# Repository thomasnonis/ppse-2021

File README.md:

# Abstract
This is the repository for SALMO, the Solar Azimuth and eLevation Motorized lOcator. It is a PCB used for driving a tracking solar panel system, using GPS location and a MPPT algorithm to maximise the incident power.  
The official name of the project is `PPS2021_SUN_TRK`

# About the project
During the second semester of the 2021/2022 A.Y. of their bachelor degree in Electronics Engineering, a group of students known as _SALMO SOCIETY_, developed a custom board to solve real world problems. 
<br>Nowadays, we are all aware about climate change and it's impact, so the _SALMO SOCIETY_ decided in partecipate to the renewable energy run, in particular exploiting the energy obtained by a solar panel to drive a load.
<br>The aim of the board it's to move the solar panel using two step motors (along z-y axis) facilitating the MPP (Maximum Power Point) reaching and, as consequence, delivering the maximum power to the load.<br> Using a GPS module, the board knows exactly where it is located around the globe; afterwards the position of the sun is computed with a specific algorithm based on astronomical calculations. Then, the spatial position of the panel is derived by the accelerometer and compass modules; lastly, the motor is moved in order to follow the exact position of the sun (given its azimuth and elevation).

# Repo structure

    📂 SALMO_pico_fw    -> Firmware 
    📂 datasheets       -> Datasheet of every component mounted on board
    📂 kicad-project    -> KiCad and gerber files 
    
# :rainbow: Building process

Debian:

    sudo apt install cmake gcc-arm-none-eabi libnewlib-arm-none-eabi build-essential

Fedora:

    sudo dnf install cmake
    sudo dnf group install "C Development Tools and Libraries" "Development Tools"
    sudo dnf install gcc-arm-linux-gnu \
    arm-none-eabi-gcc-cs-c++ \
    arm-none-eabi-gcc-cs \
    arm-none-eabi-binutils \
    arm-none-eabi-newlib

then:

    git pull
    git submodule update --init --recursive

now add to your shell profile (`~/.bashrc` or `~/.zshrc`) the current directory (pico-sdk folder) as env variable:
 
`export PICO_SDK_PATH=<path_to>/pico-sdk`

Windows:

Follow this [guide](https://shawnhymel.com/2096/how-to-set-up-raspberry-pi-pico-c-c-toolchain-on-windows-with-vs-code/#Install_MinGW-w64_GCC_Tools) and you're good to go.

Finally, in order to compile:

    cd SALMO_pico_fw
    mkdir build
    cd build 
    cmake ..
    cd src
    make -j4

After this process some binaries files will be created. <br>The suitable one is the `.uf2` file, which is located into `SALMO_pico_fw/build/src`.<br>
Now you can start the board in bootloader mode:
1. Disconnect the board
1. Hold the `BOOTSEL` button
1. Connect the device to your computer

Then drag and drop the `.uf2` file to `RPI-RP2` mass storage device.

## Picotool
If you want to install picotool and easily flash when RP2040 is not in BOOTSEL mode, you need to follow these steps:

### Debian:

    sudo apt install build-essential pkg-config libusb-1.0-0-dev

### Fedora:

    sudo dnf install libusb-devel libusb libusb1-devel systemd-devel
    sudo reboot

### Mac:

    xcode-select --install
    brew install libusb
    brew link --overwrite libusb
    
### Windows:    
For now Picotool doesn't seem to work on Windows, skip these steps and flash "manually" moving the `.uf2` file.

### Compiling Picotool
After you have downloaded picotool you have to compile it:

    cd picotool
    mkdir build
    cd build
    cmake ..
    make

Afterwards, you must give execution permissions to the scripts:

    cd ../../SALMO_pico_fw/src
    sudo chmod +x build.sh
    sudo chmod +x flash.sh
    sudo chmod +x build_and_flash.sh

If something on MacOS doesn't work use

    sudo chown -R {username}:{workgroup} ppse-2021

Then, you can simply navigate to `SALMO_pico_fw/src/` and execute `build.sh`, `flash.sh` or `build_and_flash.sh` to respectively build, flash or build and flash the project. :nail_care:

# Firmware flow chart
```mermaid
graph TB
A[Peripherals initialization] -->B(Infinite loop)
    B --> C{Is go home btn pressed?}
    C -->|Yes| D(Go home) --> E
    C -->|No| E{Is tracking enable btn pressed?}
	E -->|Yes| E1(Enable or disable tracking mode) --> F
	F{Is update_motor_position_timer elapsed <br>and tracking mode on?}
	F -->|Yes| G(Update motor position) --> H
	F -->|No| H{Is gps timer elapsed?}
	E -->|No| H
	H -->|Yes| I(Read and parse GPS output) --> L
	H -->|No| L{Is update sun position timer elapsed?}
	L -->|Yes| M(Run algorithm to compute sun position based on GPS data) --> B
	L -->|No| B
```

# How to contribute to the project
In this sections you can find some guidelines in order in order to contribute with out project

## Commits

A good commit message should be preceded by a prefix, then a colon and then a brief and descriptive comment on the changes made.  
All commits should be written in the present simple tense (eg. add file, modify this, edit that).  
Commits may also include longer descriptions in the second argument of a commit message.

Following are the prefix conventions for this repository.

- `hw:` for hardware (schematic, pcb, ...)
- `fw:` for firmware
- `sw:` for software (interfaces on a pc and such)
- `docs:` for documentation
- `notes:` for lecture notes
- `chore:` for general tasks (file management, moving stuff around, ...)

:x: `git commit -m "Added some features to code"`  
:heavy_check_mark: `git commit -m "fw: add uart implementation to gps driver"`

## File naming

All files must have no spaces and should be lowercase.

:x: Name of file.ext  
:heavy_check_mark: name-of-file.ext 

## :briefcase: Adding new drivers or libraries
If you want to add a new driver or library please keep this tree structure
```
📦 SALMO_pico_fw
 ┣📜 CMakeLists.txt (Project cmake file)
 ┣ 📂 build
 ┣ 📂 src
 ┗ 📜 CMakeLists.txt (SALMO.C cmake file)
 ┣ 📂 your_lib
 ┃ ┗ 📂 your_lib docs
 ┃ ┗ 📜 CMakeLists.txt (lib cmake file)
 ┃ ┗ 📜 your_lib.c.
 ┃ ┗ 📜 your_lib.h
```
Every library needs some sort of documentation, and of course a cmake file!

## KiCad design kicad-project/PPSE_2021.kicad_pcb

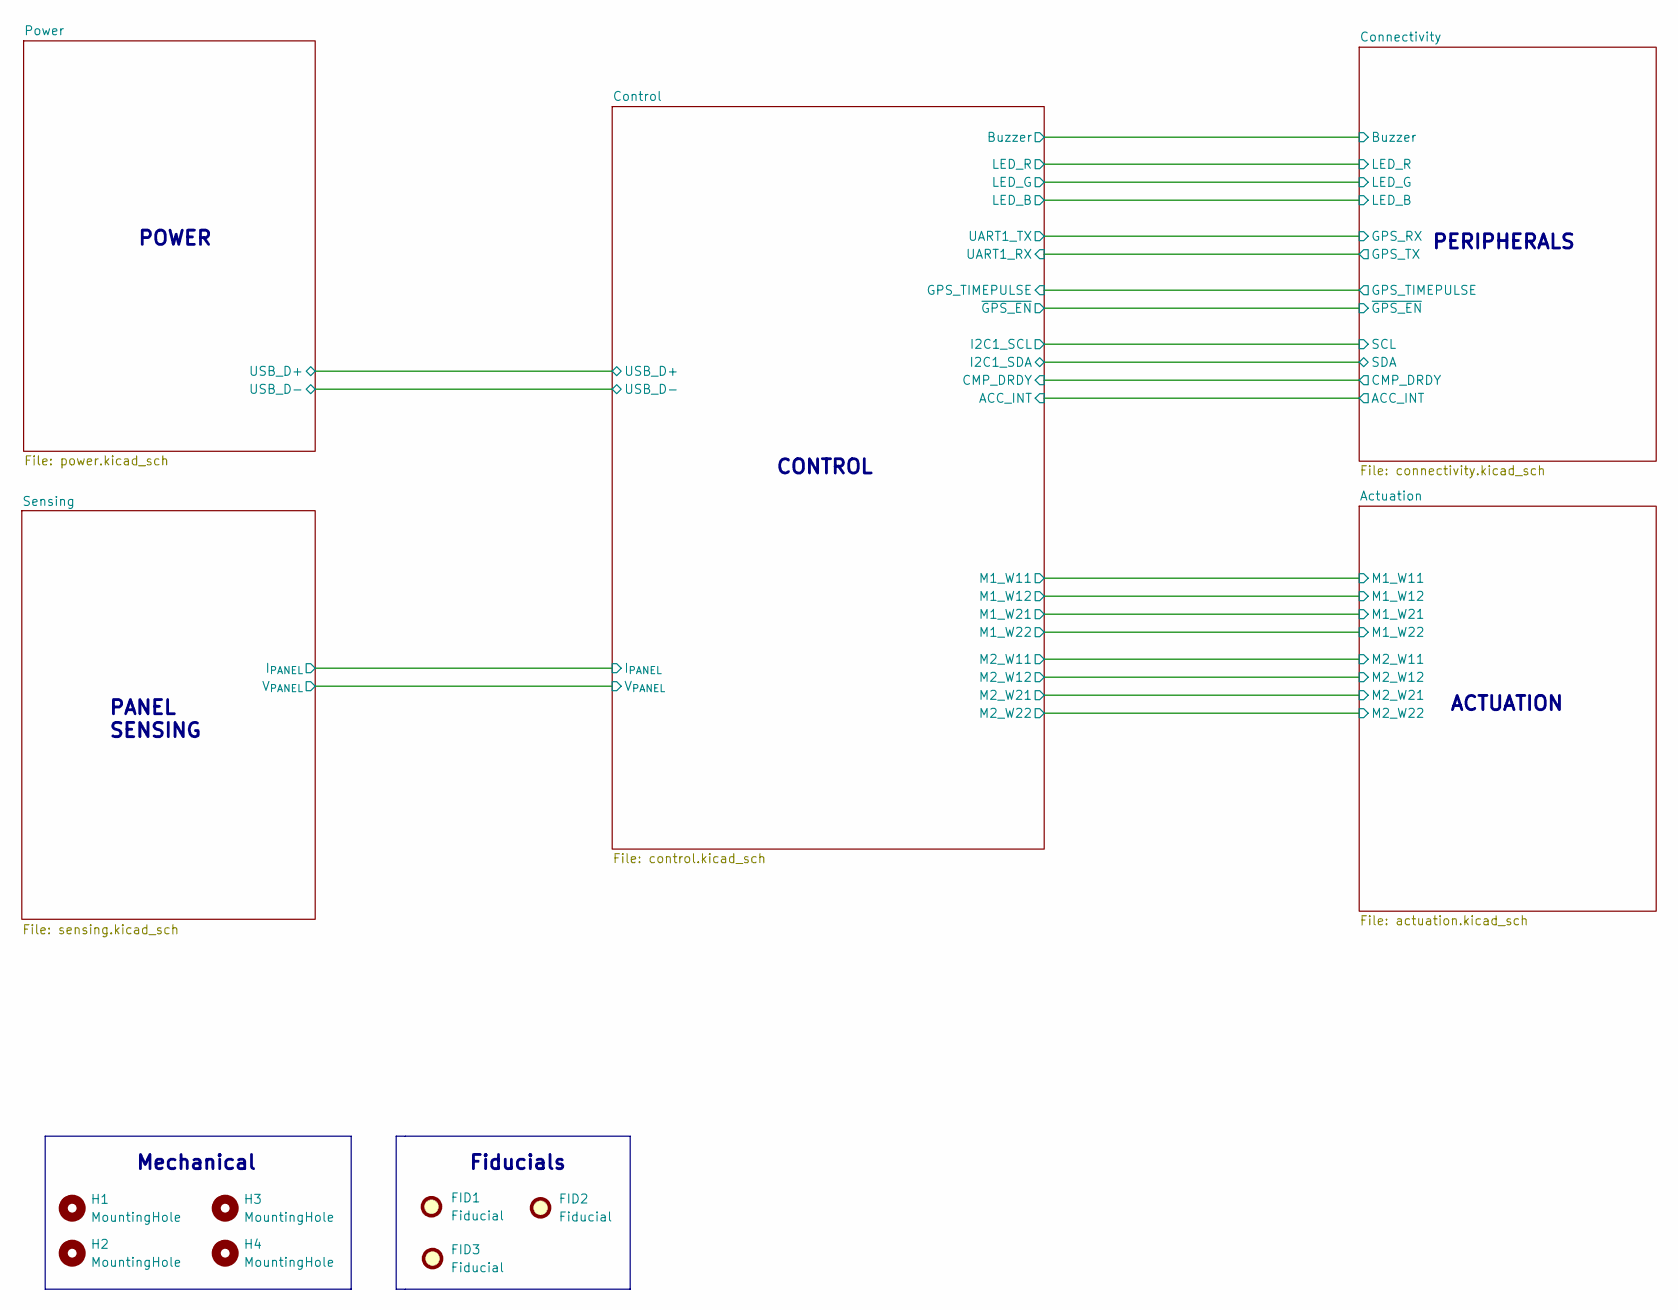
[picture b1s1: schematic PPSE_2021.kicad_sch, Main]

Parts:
FID1, FID2, FID3: Fiducial; Fiducial-ppse
H1, H2, H3, H4: MountingHole; MountingHole_3.2mm_M3

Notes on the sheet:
PERIPHERALS
PANEL SENSING
Mechanical
Fiducials
CONTROL
ACTUATION
POWER

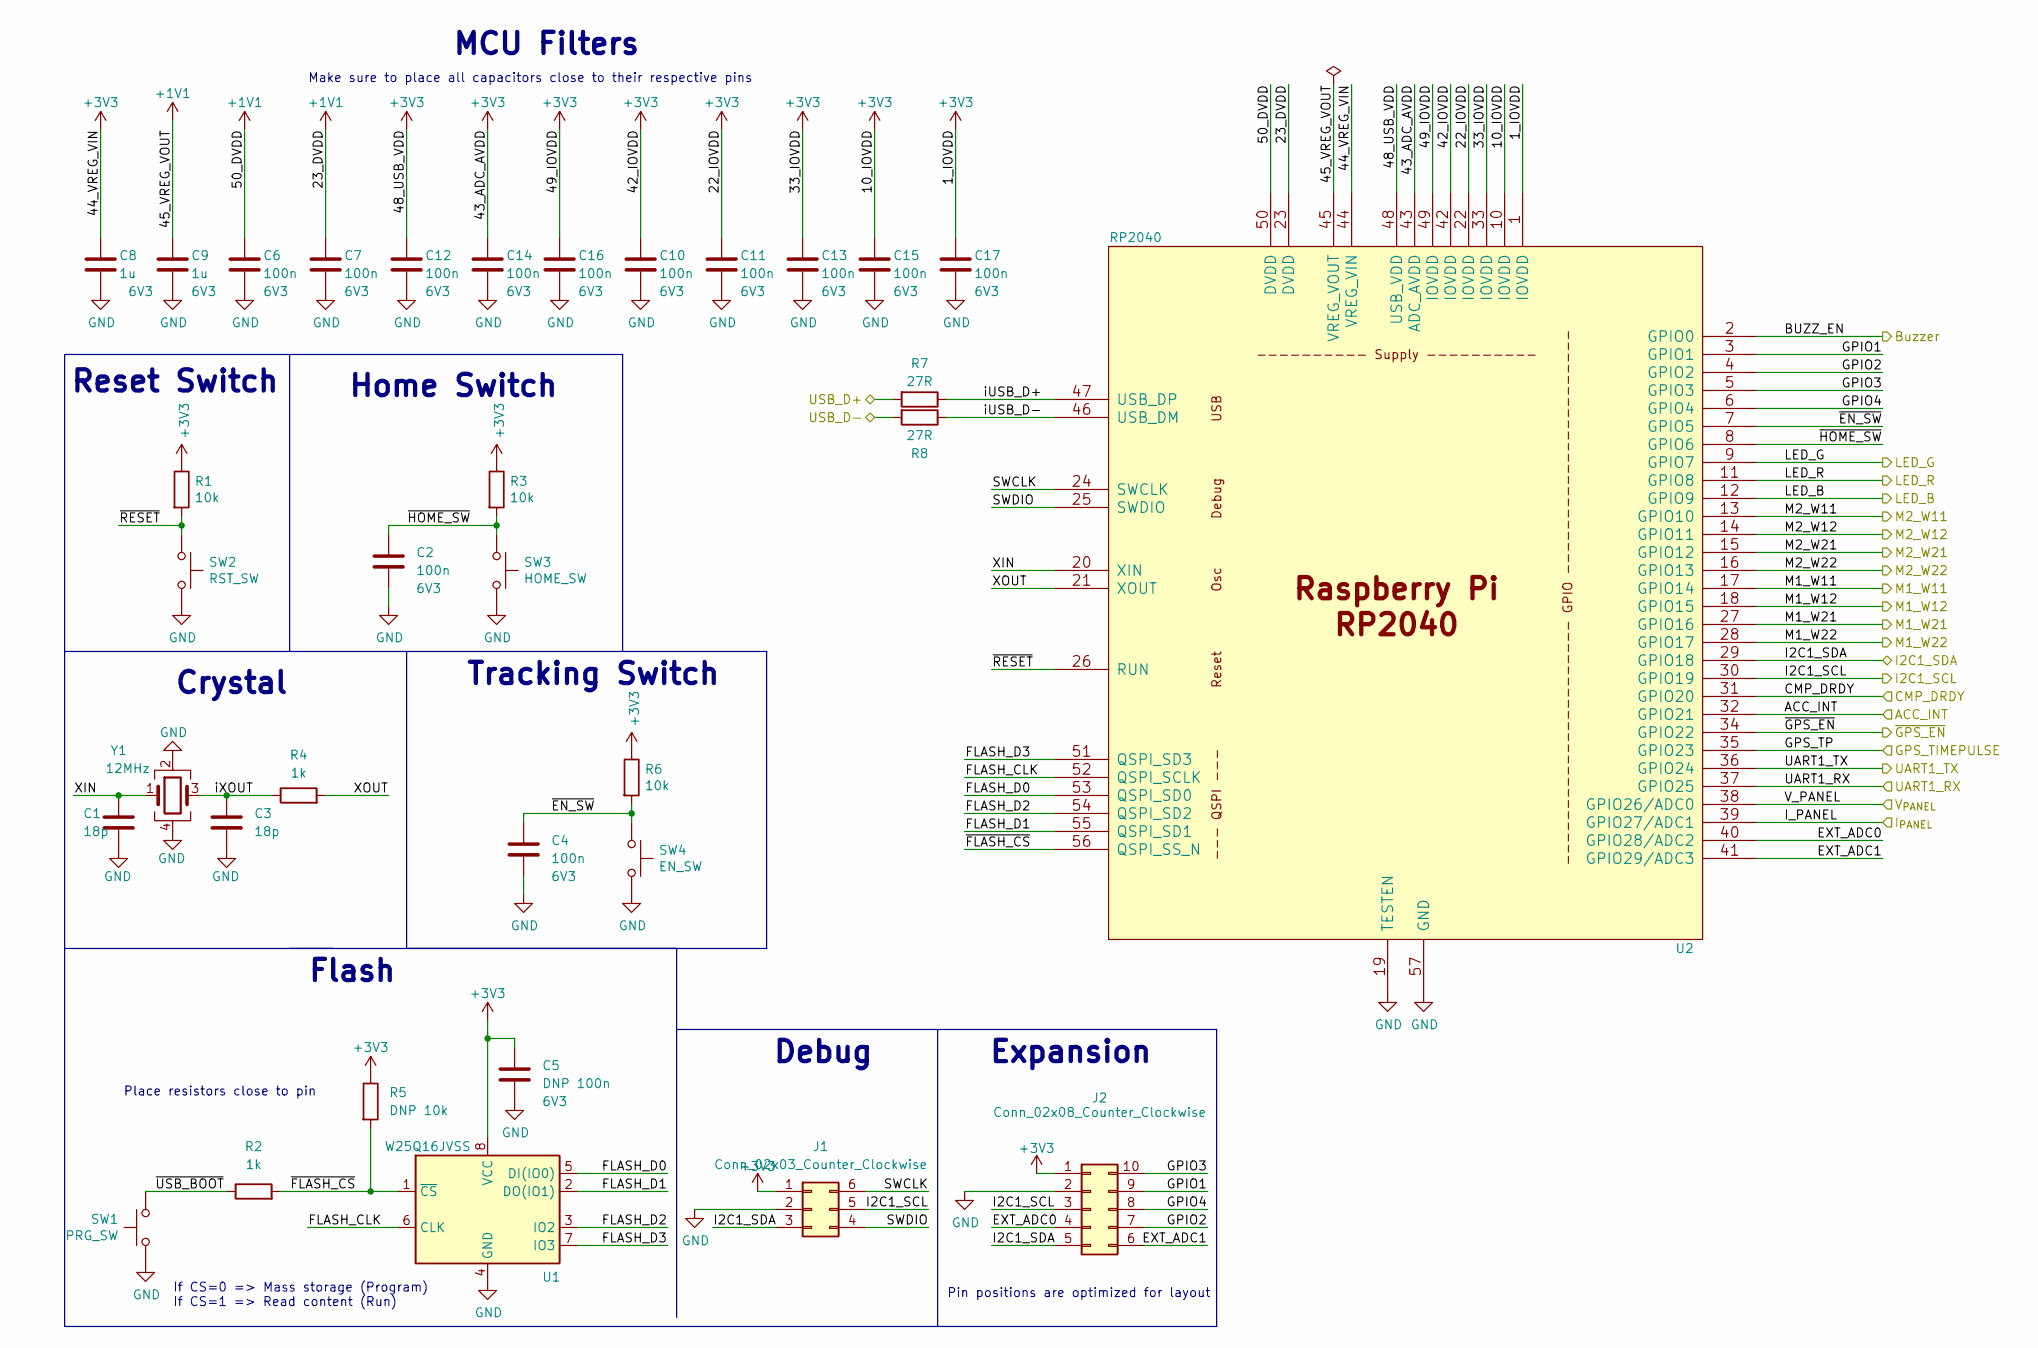
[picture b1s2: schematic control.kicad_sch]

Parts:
C1, C3: 18p; C_0603_1608Metric
C2, C4, C6, C7, C10, C11, C12, C13, C14, C15, C16, C17: 100n; C_0603_1608Metric; Voltage 6V3
C5: DNP 100n; C_0603_1608Metric; Voltage 6V3
C8, C9: 1u; C_0805_2012Metric; Voltage 6V3
J1: Conn_02x03_Counter_Clockwise; PinHeader_2x03_P2.54mm_Vertical
J2: Conn_02x08_Counter_Clockwise; PinHeader_2x05_P2.54mm_Vertical
R1, R3, R6: 10k; R_0603_1608Metric
R2, R4: 1k; R_0603_1608Metric
R5: DNP 10k; R_0603_1608Metric
R7, R8: 27R; R_0603_1608Metric
SW1: PRG_SW; SW_PUSH_6mm
SW2: RST_SW; SW_PUSH_6mm
SW3: HOME_SW; SW_PUSH_6mm
SW4: EN_SW; SW_PUSH_6mm
U1: W25Q16JVSS; SOIC-8_5.23x5.23mm_P1.27mm
U2: RP2040; RP2040-Hand-Solder
Y1: 12MHz; Crystal_SMD_3225-4Pin_3.2x2.5mm

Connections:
+1V1: C6.1, C7.1, C9.1, U2.23 (DVDD), U2.45 (VREG_VOUT), U2.50 (DVDD)
+3V3: C5.1, C8.1, C10.1, C11.1, C12.1, C13.1, C14.1, C15.1, C16.1, C17.1, J1.1, J2.1, R1.1, R3.1, R5.1, R6.1, U1.8 (VCC), U2.1 (IOVDD), U2.10 (IOVDD), U2.22 (IOVDD), U2.33 (IOVDD), U2.42 (IOVDD), U2.43 (ADC_AVDD), U2.44 (VREG_VIN), U2.48 (USB_VDD), U2.49 (IOVDD); also elsewhere on the board
/Actuation/M1_W11: U2.17 (GPIO14); also elsewhere on the board
/Actuation/M1_W12: U2.18 (GPIO15); also elsewhere on the board
/Actuation/M1_W21: U2.27 (GPIO16); also elsewhere on the board
/Actuation/M1_W22: U2.28 (GPIO17); also elsewhere on the board
/Actuation/M2_W11: U2.13 (GPIO10); also elsewhere on the board
/Actuation/M2_W12: U2.14 (GPIO11); also elsewhere on the board
/Actuation/M2_W21: U2.15 (GPIO12); also elsewhere on the board
/Actuation/M2_W22: U2.16 (GPIO13); also elsewhere on the board
/Connectivity/ACC_INT: U2.32 (GPIO21); also elsewhere on the board
/Connectivity/Buzzer: U2.2 (GPIO0); also elsewhere on the board
/Connectivity/DRDY: U2.31 (GPIO20); also elsewhere on the board
/Connectivity/GPS_EN: U2.34 (GPIO22); also elsewhere on the board
/Connectivity/GPS_RX: U2.36 (GPIO24); also elsewhere on the board
/Connectivity/GPS_TP: U2.35 (GPIO23); also elsewhere on the board
/Connectivity/GPS_TX: U2.37 (GPIO25); also elsewhere on the board
/Connectivity/SCL: J1.5, J2.3, U2.30 (GPIO19); also elsewhere on the board
/Connectivity/SDA: J1.3, J2.5, U2.29 (GPIO18); also elsewhere on the board
/Control/EXT_ADC0: J2.4, U2.40 (GPIO28/ADC2)
/Control/EXT_ADC1: J2.6, U2.41 (GPIO29/ADC3)
/Control/FLASH_CLK: U1.6 (CLK), U2.52 (QSPI_SCLK)
/Control/FLASH_D0: U1.5 (DI(IO0)), U2.53 (QSPI_SD0)
/Control/FLASH_D1: U1.2 (DO(IO1)), U2.55 (QSPI_SD1)
/Control/FLASH_D2: U1.3 (IO2), U2.54 (QSPI_SD2)
/Control/FLASH_D3: U1.7 (IO3), U2.51 (QSPI_SD3)
/Control/GPIO1: J2.9, U2.3 (GPIO1)
/Control/GPIO2: J2.7, U2.4 (GPIO2)
/Control/GPIO3: J2.10, U2.5 (GPIO3)
/Control/GPIO4: J2.8, U2.6 (GPIO4)
/Control/I_PANEL: U2.39 (GPIO27/ADC1); also elsewhere on the board
/Control/LED_B: U2.12 (GPIO9); also elsewhere on the board
/Control/LED_G: U2.9 (GPIO7); also elsewhere on the board
/Control/LED_R: U2.11 (GPIO8); also elsewhere on the board
/Control/SWCLK: J1.6, U2.24 (SWCLK)
/Control/SWDIO: J1.4, U2.25 (SWDIO)
/Control/USB_D+: R7.2; also elsewhere on the board
/Control/USB_D-: R8.2; also elsewhere on the board
/Control/V_PANEL: U2.38 (GPIO26/ADC0); also elsewhere on the board
/Control/XIN: C1.1, U2.20 (XIN), Y1.1
/Control/XOUT: R4.2, U2.21 (XOUT)
/Control/iUSB_D+: R7.1, U2.47 (USB_DP)
/Control/iUSB_D-: R8.1, U2.46 (USB_DM)
/Control/iXOUT: C3.1, R4.1, Y1.3
/Control/~EN_SW: C4.1, R6.2, SW4.1, U2.7 (GPIO5)
/Control/~FLASH_CS: R2.2, R5.2, U1.1 (~CS), U2.56 (QSPI_SS_N)
/Control/~HOME_SW: C2.1, R3.2, SW3.1, U2.8 (GPIO6)
/Control/~RESET: R1.2, SW2.1, U2.26 (RUN)
/Control/~USB_BOOT: R2.1, SW1.1
GND: C1.2, C2.2, C3.2, C4.2, C5.2, C6.2, C7.2, C8.2, C9.2, C10.2, C11.2, C12.2, C13.2, C14.2, C15.2, C16.2, C17.2, J1.2, J2.2, SW1.2, SW2.2, SW3.2, SW4.2, U1.4 (GND), U2.19 (TESTEN), U2.57 (GND), Y1.2, Y1.4; also elsewhere on the board

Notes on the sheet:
Expansion
Place resistors close to pin
MCU Filters
Home Switch
Make sure to place all capacitors close to their respective pins
Tracking Switch
Pin positions are optimized for layout
Flash
Debug
Reset Switch
If CS=0 => Mass storage (Program) If CS=1 => Read content (Run)
Crystal

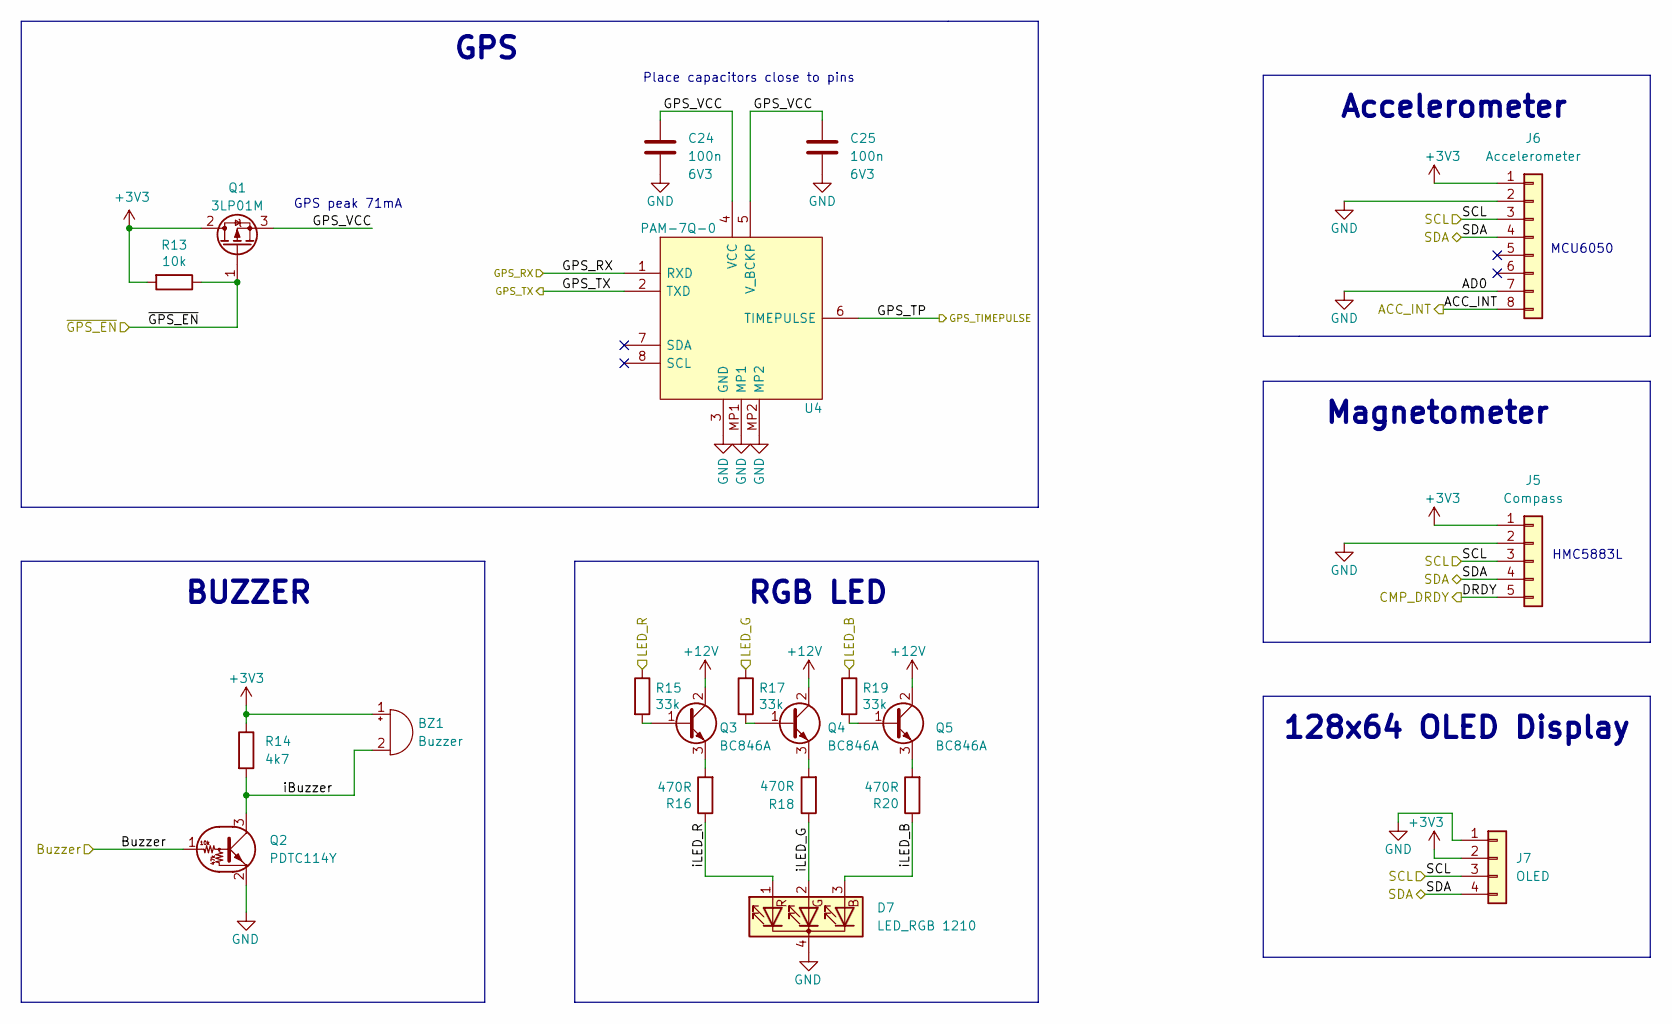
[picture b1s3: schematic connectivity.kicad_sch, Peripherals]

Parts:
BZ1: Buzzer; Buzzer_12x9.5RM7.6
C24, C25: 100n; C_0603_1608Metric; Voltage 6V3
D7: LED_RGB 1210; LED_RGB_1210
J5: Compass; PinHeader_1x05_P2.54mm_Horizontal
J6: Accelerometer; PinHeader_1x08_P2.54mm_Horizontal
J7: OLED; PinHeader_1x04_P2.54mm_Vertical
Q1: 3LP01M; SOT-323_SC-70
Q2: PDTC114Y; SOT-23
Q3, Q4, Q5: BC846A; SOT-23
R13: 10k; R_0603_1608Metric
R14: 4k7; R_0603_1608Metric
R15, R17, R19: 33k; R_0603_1608Metric
R16, R18, R20: 470R; R_0603_1608Metric
U4: PAM-7Q-0; PAM-7Q0; Manufacturer_Part_Number PAM-7Q-0

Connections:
+3V3: BZ1.1 (-), J5.1, J6.1, J7.2, Q1.2 (D), R13.2, R14.1; also elsewhere on the board
+12V: Q3.2 (C), Q4.2 (C), Q5.2 (C); also elsewhere on the board
/Connectivity/ACC_INT: J6.8; also elsewhere on the board
/Connectivity/Buzzer: Q2.1 (B); also elsewhere on the board
/Connectivity/DRDY: J5.5; also elsewhere on the board
/Connectivity/GPS_EN: Q1.1 (G), R13.1; also elsewhere on the board
/Connectivity/GPS_RX: U4.1 (RXD); also elsewhere on the board
/Connectivity/GPS_TP: U4.6 (TIMEPULSE); also elsewhere on the board
/Connectivity/GPS_TX: U4.2 (TXD); also elsewhere on the board
/Connectivity/GPS_VCC: C24.1, C25.1, Q1.3 (S), U4.4 (VCC), U4.5 (V_BCKP)
/Connectivity/SCL: J5.3, J6.3, J7.3; also elsewhere on the board
/Connectivity/SDA: J5.4, J6.4, J7.4; also elsewhere on the board
/Connectivity/iBuzzer: BZ1.2 (+), Q2.3 (C), R14.2
/Connectivity/iLED_B: D7.3 (BA), R20.1
/Connectivity/iLED_G: D7.2 (GA), R18.1
/Connectivity/iLED_R: D7.1 (RA), R16.1
/Control/LED_B: R19.1; also elsewhere on the board
/Control/LED_G: R17.1; also elsewhere on the board
/Control/LED_R: R15.1; also elsewhere on the board
GND: C24.2, C25.2, D7.4 (K), J5.2, J6.2, J6.7, J7.1, Q2.2 (E), U4.3 (GND), U4.MP1, U4.MP2; also elsewhere on the board
unnamed: Q3.1 (B), R15.2
unnamed: Q3.3 (E), R16.2
unnamed: Q4.1 (B), R17.2
unnamed: Q4.3 (E), R18.2
unnamed: Q5.1 (B), R19.2
unnamed: Q5.3 (E), R20.2

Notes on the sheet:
MCU6050
Accelerometer
RGB LED
Magnetometer
HMC5883L
GPS peak 71mA
128x64 OLED Display
BUZZER
GPS
Place capacitors close to pins

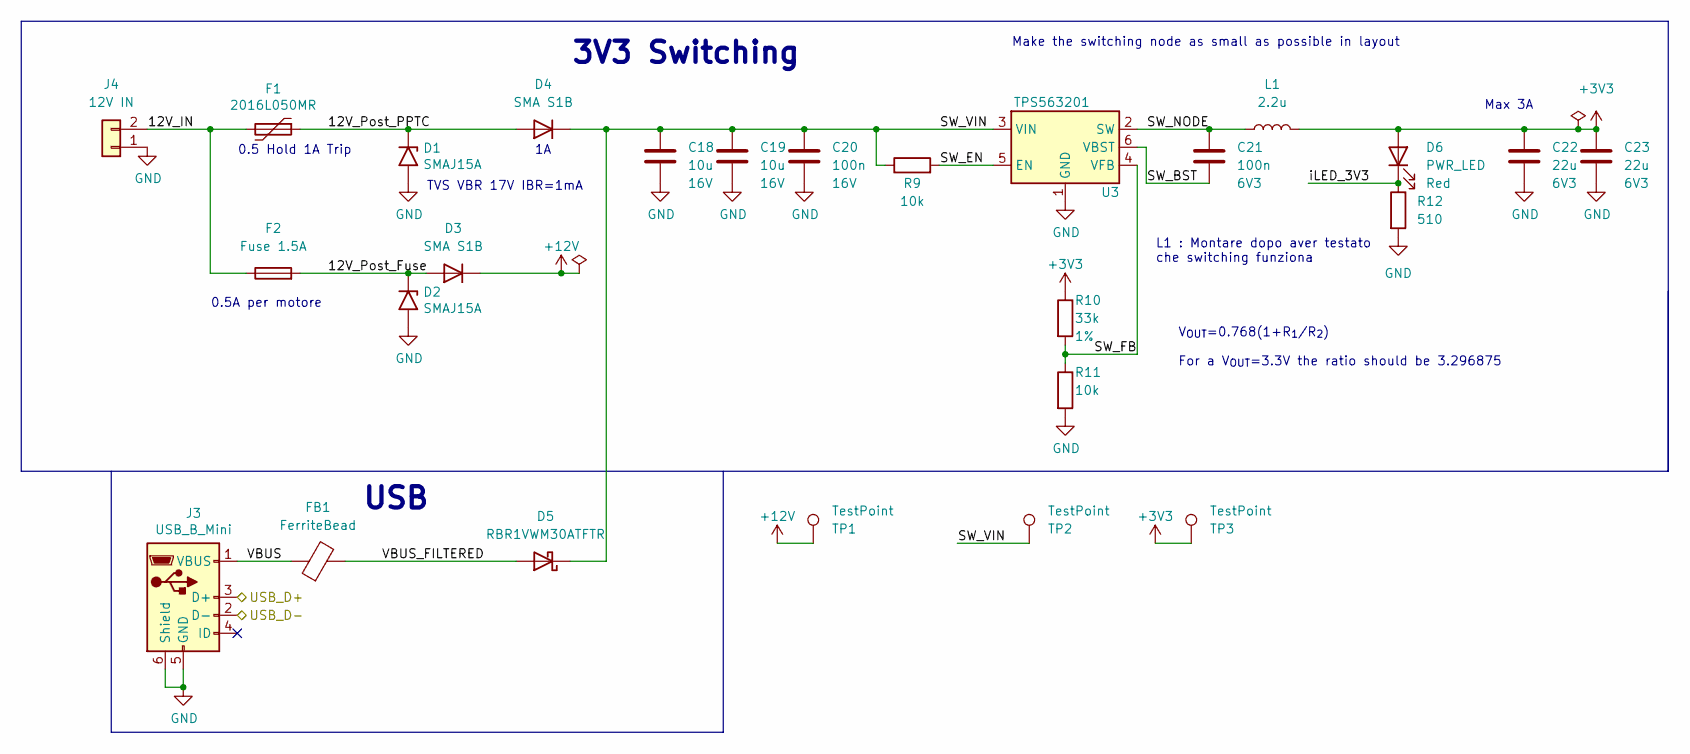
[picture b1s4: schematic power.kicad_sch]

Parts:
C18, C19: 10u; C_0805_2012Metric; Voltage 16V
C20: 100n; C_0603_1608Metric; Voltage 16V
C21: 100n; C_0603_1608Metric; Voltage 6V3
C22, C23: 22u; C_0805_2012Metric; Voltage 6V3
D1, D2: SMAJ15A; D_SMA
D3, D4: SMA S1B; D_SMA
D5: RBR1VWM30ATFTR; Package-PMDE
D6: PWR_LED; LED_0603_1608Metric
F1: 2016L050MR; 2016L Series PPTC
F2: Fuse 1.5A; Fuse Holder
FB1: FerriteBead; L_0603_1608Metric
J3: USB_B_Mini; USB_Mini-B_Wuerth_65100516121_Horizontal
J4: 12V IN; Molex_Micro-Fit_3.0_43650-0200_1x02_P3.00mm_Horizontal
L1: 2.2u; Inductor
R9, R11: 10k; R_0603_1608Metric
R10: 33k; R_0603_1608Metric; Tolerance 1%
R12: 510; R_0603_1608Metric
TP1, TP2, TP3: TestPoint; TestPoint_Keystone_5005-5009_Compact
U3: TPS563201; SOT-23-6

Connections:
+3V3: C22.1, C23.1, D6.2 (A), L1.2, R10.1, TP3.1; also elsewhere on the board
+12V: D3.1 (K), TP1.1; also elsewhere on the board
/Control/USB_D+: J3.3 (D+); also elsewhere on the board
/Control/USB_D-: J3.2 (D-); also elsewhere on the board
/Power/12V_IN: F1.2, F2.1, J4.2
/Power/12V_Post_Fuse: D2.1 (A1), D3.2 (A), F2.2
/Power/12V_Post_PPTC: D1.1 (A1), D4.2 (A), F1.1
/Power/SW_BST: C21.2, U3.6 (VBST)
/Power/SW_EN: R9.2, U3.5 (EN)
/Power/SW_FB: R10.2, R11.1, U3.4 (VFB)
/Power/SW_NODE: C21.1, L1.1, U3.2 (SW)
/Power/SW_VIN: C18.1, C19.1, C20.1, D4.1 (K), D5.1 (K), R9.1, TP2.1, U3.3 (VIN)
/Power/VBUS: FB1.1, J3.1 (VBUS)
/Power/VBUS_FILTERED: D5.2 (A), FB1.2
/Power/iLED_3V3: D6.1 (K), R12.1
GND: C18.2, C19.2, C20.2, C22.2, C23.2, D1.2 (A2), D2.2 (A2), J3.5 (GND), J3.6 (Shield), J4.1, R11.2, R12.2, U3.1 (GND); also elsewhere on the board

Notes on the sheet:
Max 3A
0.5 Hold 1A Trip
3V3 Switching
0.5A per motore
Make the switching node as small as possible in layout
USB
TVS VBR 17V IBR=1mA
L1 : Montare dopo aver testato che switching funziona
V_{OUT}=0.768(1+R_{1}/R_{2}) For a V_{OUT}=3.3V the ratio should be 3.296875

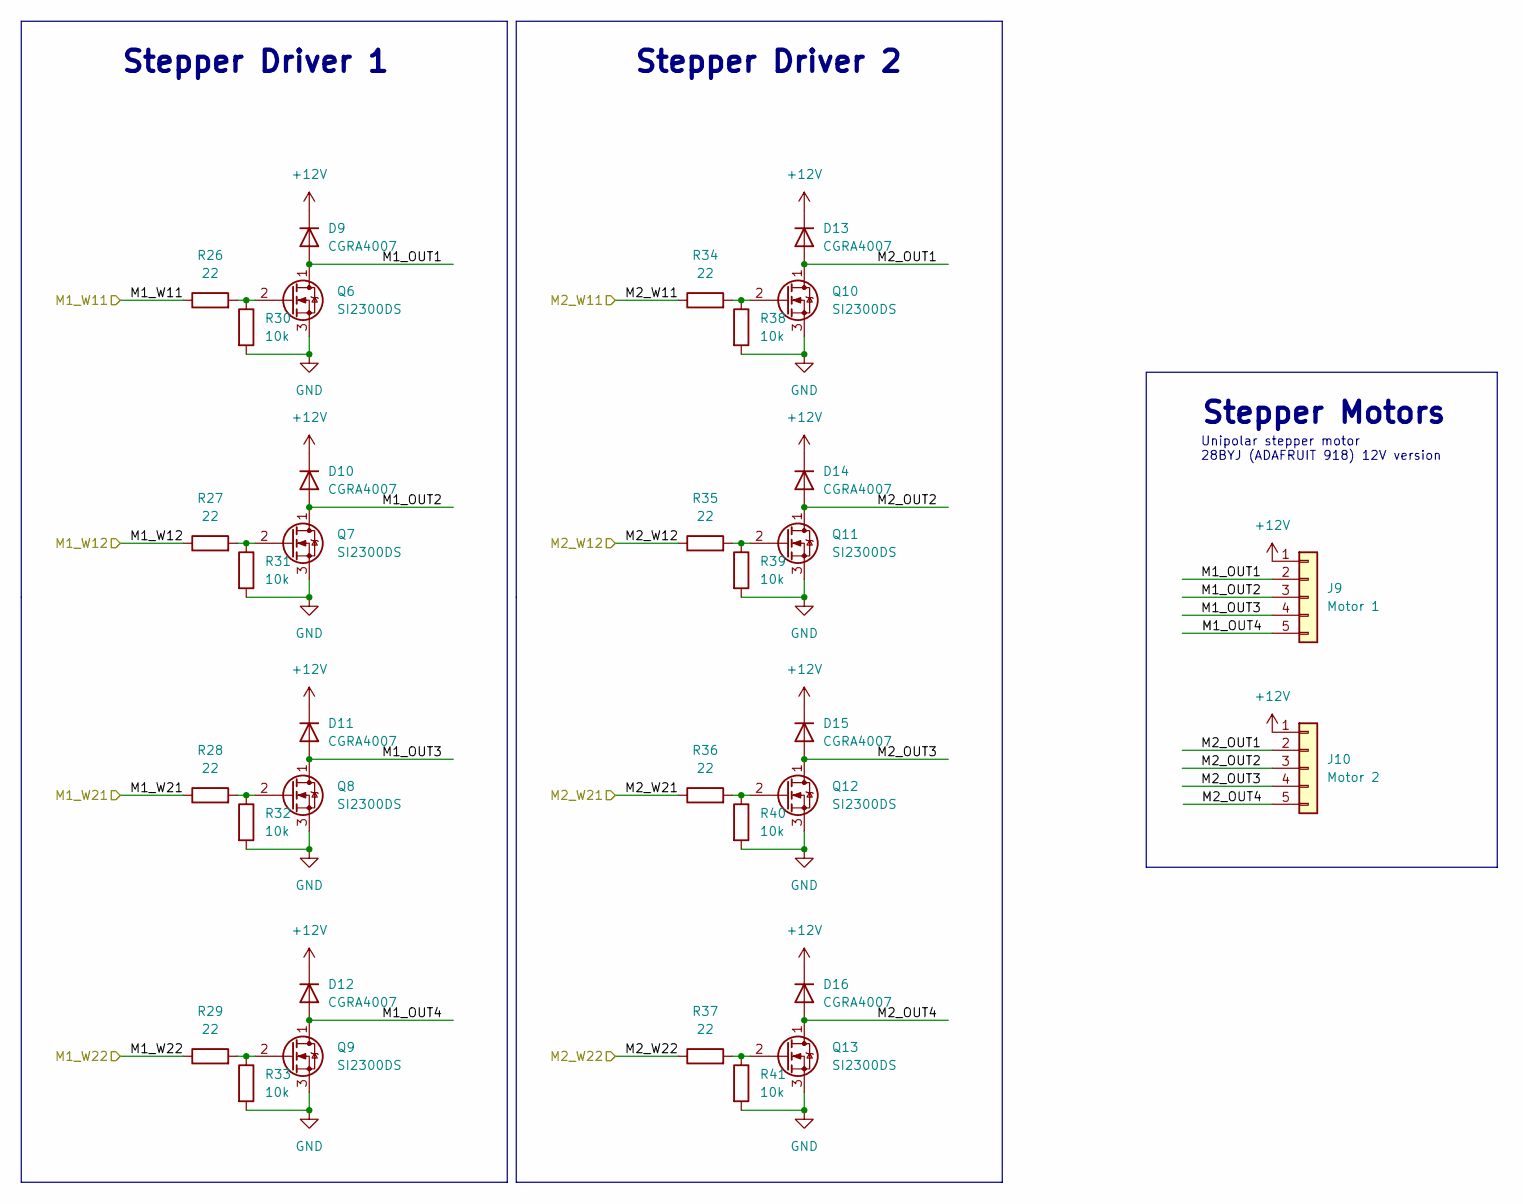
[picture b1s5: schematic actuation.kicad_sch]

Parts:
D9, D10, D11, D12, D13, D14, D15, D16: CGRA4007; D_SMA
J9: Motor 1; JST_XH_S5B-XH-A_1x05_P2.50mm_Horizontal
J10: Motor 2; JST_XH_S5B-XH-A_1x05_P2.50mm_Horizontal
Q6, Q7, Q8, Q9, Q10, Q11, Q12, Q13: SI2300DS; SOT-23
R26, R27, R28, R29, R34, R35, R36, R37: 22; R_0603_1608Metric
R30, R31, R32, R33, R38, R39, R40, R41: 10k; R_0603_1608Metric

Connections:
+12V: D9.1 (K), D10.1 (K), D11.1 (K), D12.1 (K), D13.1 (K), D14.1 (K), D15.1 (K), D16.1 (K), J9.1, J10.1; also elsewhere on the board
/Actuation/M1_OUT1: D9.2 (A), J9.2, Q6.1 (D)
/Actuation/M1_OUT2: D10.2 (A), J9.3, Q7.1 (D)
/Actuation/M1_OUT3: D11.2 (A), J9.4, Q8.1 (D)
/Actuation/M1_OUT4: D12.2 (A), J9.5, Q9.1 (D)
/Actuation/M1_W11: R26.1; also elsewhere on the board
/Actuation/M1_W12: R27.1; also elsewhere on the board
/Actuation/M1_W21: R28.1; also elsewhere on the board
/Actuation/M1_W22: R29.1; also elsewhere on the board
/Actuation/M2_OUT1: D13.2 (A), J10.2, Q10.1 (D)
/Actuation/M2_OUT2: D14.2 (A), J10.3, Q11.1 (D)
/Actuation/M2_OUT3: D15.2 (A), J10.4, Q12.1 (D)
/Actuation/M2_OUT4: D16.2 (A), J10.5, Q13.1 (D)
/Actuation/M2_W11: R34.1; also elsewhere on the board
/Actuation/M2_W12: R35.1; also elsewhere on the board
/Actuation/M2_W21: R36.1; also elsewhere on the board
/Actuation/M2_W22: R37.1; also elsewhere on the board
GND: Q6.3 (S), Q7.3 (S), Q8.3 (S), Q9.3 (S), Q10.3 (S), Q11.3 (S), Q12.3 (S), Q13.3 (S), R30.2, R31.2, R32.2, R33.2, R38.2, R39.2, R40.2, R41.2; also elsewhere on the board
unnamed: Q6.2 (G), R26.2, R30.1
unnamed: Q7.2 (G), R27.2, R31.1
unnamed: Q8.2 (G), R28.2, R32.1
unnamed: Q9.2 (G), R29.2, R33.1
unnamed: Q10.2 (G), R34.2, R38.1
unnamed: Q11.2 (G), R35.2, R39.1
unnamed: Q12.2 (G), R36.2, R40.1
unnamed: Q13.2 (G), R37.2, R41.1

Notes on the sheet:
Stepper Motors
Unipolar stepper motor 28BYJ (ADAFRUIT 918) 12V version
Stepper Driver 2
Stepper Driver 1

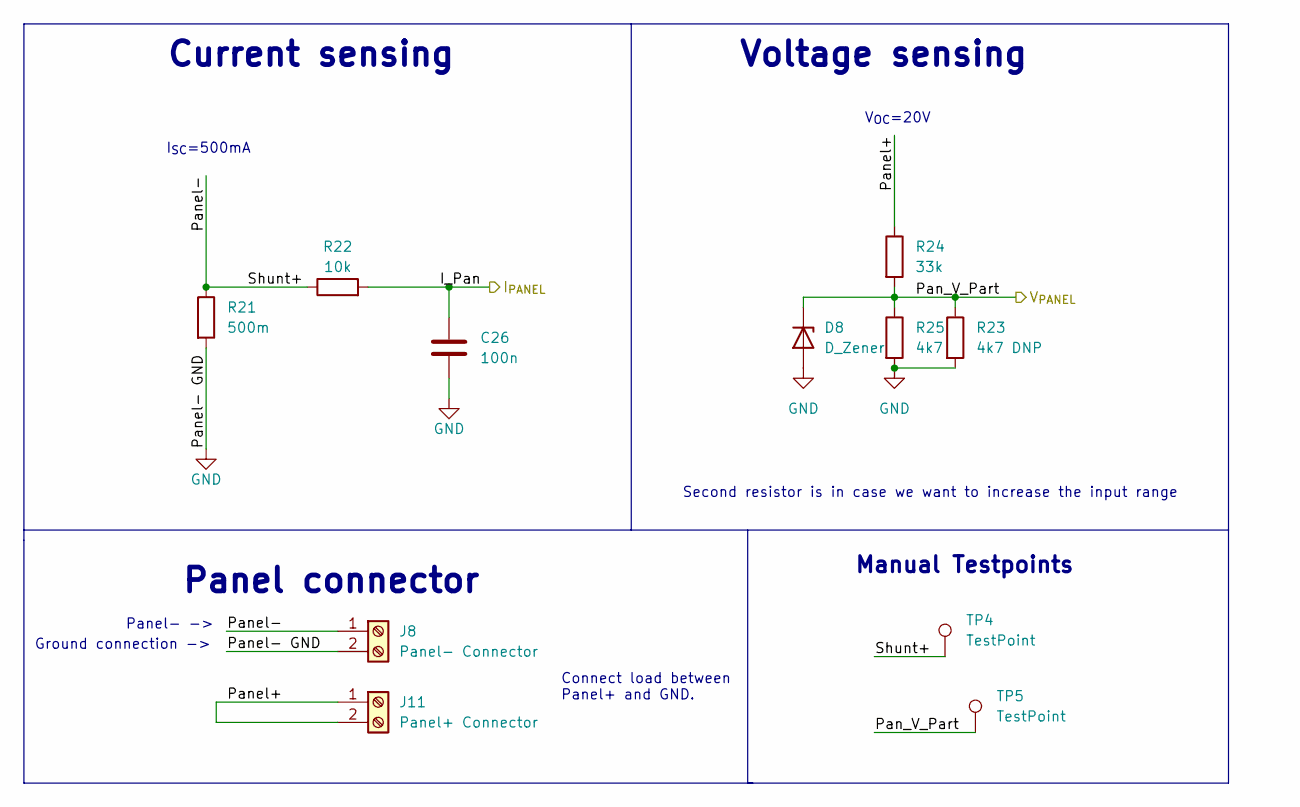
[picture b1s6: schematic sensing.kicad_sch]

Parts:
C26: 100n; C_0603_1608Metric
D8: D_Zener; D_0603_1608Metric
J8: Panel- Connector; TerminalBlock_TE_282834-2_1x02_P2.54mm_Horizontal
J11: Panel+ Connector; TerminalBlock_TE_282834-2_1x02_P2.54mm_Horizontal
R21: 500m; R_1210_3225Metric
R22: 10k; R_0603_1608Metric
R23: 4k7 DNP; R_0603_1608Metric
R24: 33k; R_0603_1608Metric
R25: 4k7; R_0603_1608Metric
TP4, TP5: TestPoint; TestPoint_Keystone_5005-5009_Compact

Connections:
/Control/I_PANEL: C26.1, R22.2; also elsewhere on the board
/Control/V_PANEL: D8.1 (K), R23.1, R24.2, R25.1, TP5.1; also elsewhere on the board
/Sensing/Panel+: J11.1, J11.2, R24.1
/Sensing/Panel-: J8.1, R21.1, R22.1, TP4.1
GND: C26.2, D8.2 (A), J8.2, R21.2, R23.2, R25.2; also elsewhere on the board

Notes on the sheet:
Second resistor is in case we want to increase the input range
Voltage sensing
Current sensing
I_{SC}=500mA
V_{OC}=20V
Connect load between Panel+ and GND.
Panel connector
Panel- ->
Ground connection ->
Manual Testpoints

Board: 2 copper layers, 133 parts (0 on the bottom side), 91 nets, no tracks yet.

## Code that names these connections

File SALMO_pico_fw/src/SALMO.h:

/**
 * @file SALMO.h
 * @author SALMO Society
 * @brief Salmo configuration file
 * @version 0.1
 * @date 2022-04-11
 *
 * @copyright Copyright (c) 2022
 *
 */

#define BUZZ_EN 0
#define GPIO1 1
#define GPIO2 2
#define GPIO3 3
#define GPIO4 4
#define NOT_EN_SW 5
#define NOT_HOME_SW 6
#define LED_G 7
#define LED_R 8
#define LED_B 9
#define M2_W11 10
#define M2_W12 11
#define M2_W21 12
#define M2_W22 13
#define M1_W11 14
#define M1_W12 15
#define M1_W21 16
#define M1_W22 17
#define I2C1_SDA 18
#define I2C1_SCL 19
#define CMP_DRDY 20
#define ACC_INT 21
#define GPS_EN 22 // When GPS is enabled, the GPS_EN pin is pulled low
#define GPS_TP 23
#define UART1_TX 24
#define UART1_RX 25
#define V_PANEL 26
#define I_PANEL 27
#define EXT_ADC0 28
#define EXT_ADC1 29

#define I2C_PERIPHERAL (i2c1)
#define I2C_PORT1_BAUD_RATE 400 * 1000

#define STEPS_PER_REV 200
#define INITIAL_SPEED 50

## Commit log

2022-03-10 sch: add notes and circuits from 2022/03/10 lecture
2022-03-10 notes: add constraints from 2022/03/10 lecture
2022-03-10 fw: add project folder
2022-03-10 docs: add sdk documentation pdfs
2022-03-10 report: add more PIO info
2022-03-11 sch: add gps
2022-03-15 fw: add tracking algorithm papers and some functions
2022-03-17 fw: fix submodules
2022-03-17 hw: add block diagram
2022-03-17 hw: migrate to kicad 6
2022-03-17 hw: add RP2040 footprint for hand soldering
2022-03-17 report: remove personal report
2022-03-17 chore: add README
2022-03-17 chore: fix README tick and cross
2022-03-17 chore: fix README commit order
2022-03-18 hw: fix crystal topology
2022-03-23 hw: add flash, switching circuit and XOUT resistor, change GPS and general cleanup
2022-03-23 chore: add official project name to README
2022-03-23 hw: update block diagram
2022-03-23 hw: add panel sensing and change GPS_EN to hierarchical pin
2022-03-23 fw: first algo draft
2022-03-23 fw: added MPU9250
2022-03-23 added MPU9250 Datasheet
2022-03-24 added mm7150 datasheet
2022-03-24 hw: added MBR120VLSFT1G to footprints
2022-03-24 fw: broken stuff for simo
2022-03-24 fw: fixed lmst
2022-03-24 fw: params fixed, except to elevation and azimuth + added calculations spreadsheet
2022-03-25 added useful data and improved gmst calc
2022-03-25 added useful data for lmst
2022-03-25 added ra_dec.ods doc
2022-03-25 corrected some things and probably found a big error on real longitude (ecliptic long)
2022-03-25 docs: re-add datasheets that were removed and rename mpu9250
2022-03-25 hw: add limit switches, dual power input, actuation sheet, debug and expansion connectors and connect sheets
2022-03-25 fw: algo v0.90
2022-03-25 docs: moved noaa excel calcs to docs folder
2022-03-25 fw: solltimy removed some useless functions
2022-03-26 fw: added struct for place and wrapped whole computation into compute_complete_position function
2022-03-26 fw: algo V1.0
2022-03-26 updated .gitignore
2022-03-26 removed useless files
2022-03-26 other: added readme
2022-03-26 fw: removed timezone and updated readme with funny stuffs
2022-03-28 fw: added inline args
2022-03-28 other: added submodules
2022-03-28 fw: added TinyUSB as submodule
2022-03-28 hw: schematic updates
2022-03-29 hw: connect filtering capacitor near vdd pin
2022-03-29 hw: update schematic pt. 2
    add switching enable resistor, change usb inductor to ferrite bead, add OR gate and microstepping solder jumpers to motor driver, remove i2c and backup supply solder jumper from GPS, add ferrite bead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
2022-03-29 fw: added MM7150 sample code
2022-03-30 hw: added MAN_NORD and TRCK_ON_OFF buttons and OLED Display
2022-03-30 hw: set grid to 50 mils and missing labels
2022-03-30 hw: add stepper motor drivers
2022-03-31 hw: move inputs from control to sensing and outputs from control to actuation
2022-03-31 hw: add TVS diode and comments
2022-03-31 fw: discrete dirver for stepper
2022-03-31 hw: add capacitor voltages, fix supply caps and other fixes
    add capacitor voltages, change polarized caps to normal, move switching capacitors, remove 5V power, fix switching ballast capacitor, remove switching feedback capacitor, switch sensing and actuation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
2022-04-02 hw: add connectors and crystal footprints
2022-04-03 hw: add footprints for resistors and capacitors and re-add specs documant that was deleted
2022-04-04 hw: update root pin and usb connector
2022-04-04 hw: rgb led with NPN
2022-04-04 docs: add ferrite, diode and dual opamp datasheets
2022-04-04 hw: part of last checks and footprint assignments
2022-04-04 commit anonimo di thimas
2022-04-05 hw: add mounting holes
2022-04-05 hw: add PMDE footprint
2022-04-05 hw: add last footprints
2022-04-05 hw: first layout draft
2022-04-07 hw: classroom changes
2022-04-07 hw: add fiducial to eeschema and change sw footprints
2022-04-08 change mcu pins and optimize layout
2022-04-08 hw: power routing
2022-04-08 hw: first round of routing
2022-04-09 hw: finalize routing (dbg uart missing)
2022-04-09 fw: setted env for rp2040
2022-04-09 fw: submodule updates
2022-04-09 fw: makefile configuration and tutorial
2022-04-09 fw: added build and build_and_flash scripts
2022-04-09 fw: partially fix makefile
2022-04-09 fw:updated build.sh
2022-04-09 fw: fix building libraries with cmake
2022-04-10 fw: changed compute_complete_position function
2022-04-11 fw: removed useless things on CMakeLists
2022-04-11 fw: added MPU6050 driver repo
2022-04-11 hw: final changes
2022-04-11 fw: things
2022-04-11 docs: add schematic pdf
2022-04-11 fw: fix printf and algo warnings
2022-04-11 fw: MPU6050 impr.
2022-04-11 fw: mpu6050 v1
2022-04-11 fw: added HMC5883L library
2022-04-11 fw: started HMC5883L
2022-04-11 docs: updated readme
2022-04-12 hw: add gerber files
2022-04-12 hw: small fixes to vias and silkscreen
2022-04-12 fw: HMC5883L driver V0.9 BAD
2022-04-13 hw: add sensing resistance values
2022-04-13 fw: HMC5883L driver V1.0 bad
2022-04-13 fw: added SSD1306
2022-04-13 hw: final pcb check before submit
2022-04-21 OLED 0.9
2022-04-21 OLED 0.91
2022-04-25 OLED V1.0
2022-04-25 fw: added submodule picotool
2022-04-25 fw: now you can flash without bootsel mode
2022-04-27 deleted kicad folder
2022-04-28 fw: add timer and gps emulator
2022-04-28 fix: merge target libraries salmo cmake
2022-04-28 fw: HMC5883L V1.1
2022-05-02 fix: HMC default address wrong define
2022-05-02 change: removed tinyusb submodule
2022-05-05 fw: add stepper
2022-05-05 fw: errata: add stepper
2022-05-09 fw: update stepper folder
2022-05-12 fw: updates
2022-05-12 scripts fix
2022-05-25 fw: working setuo
2022-05-25 fw: add nmea-parser template
2022-05-25 fw: test HMC
2022-06-03 fw: add gps read and parse
2022-06-05 fw: [tracking-algo] seconds returned to be double instead of int
2022-06-05 fw chore: remove sample test position
2022-06-05 fw: add test with different locations. Tracking based on minutes is not working
2022-06-19 docs: add cmake and arm toolchain to requirements
2022-06-19 fw: MPU6050 I2C calls now are non blocking
2022-06-19 fw: start HMC5883L conversion (I2C function independecy)
2022-06-19 fw: fix compiling out of build folder if build folder not present before compiling first time with all argument
2022-06-19 fw: non blocking and I2C funct. independent HMC driver
2022-06-19 fw: add compass headings and home button irq
2022-06-19 chore: fix typo
2022-06-20 chore: merged hw stuff with fw branch and fw: full home btn feature
2022-06-20 chore: clean useless files
2022-06-20 chore: removed Relazione.docx from tracked files
2022-06-20 fw: fix compilation errors
2022-06-27 hw: add custom page layout
2022-06-27 feat: add motor function with buttons
2022-06-27 chore: removed second readme
2022-06-28 chore: add firmware flow chart
2022-06-28 chore: add sdk submodules
2022-06-28 docs: update schematic pdf (SALMO Society logo is broken)
2022-06-28 docs: fix missing flowchart on readme
2022-06-28 chore: add define to timers timeout
2022-06-28 chore: update radme with more clear cmake references
2022-06-28 hw: changes for the simia
2022-06-29 hw: change some small notes
2022-06-29 hw: exported pdf with changes
2022-06-29 docs: add quartz datasheet
2022-06-29 fw: conformed HMC driver with MPU driver form
2022-06-29 fw: moved PAM7Q init into a separate driver folder
2022-06-30 fw: updated copyright notices
2022-06-30 fw: fix timegm implicit declaration warning
2022-06-30 report: add screenshots of steps of layout
2022-06-30 fw: minor style changes in SALMO.c
    chore: update pico-sdk to 1.40 and picotool
2022-06-30 doc: remove old datasheets folder
2022-06-30 doc: add update datasheets folder
2022-06-30 chore: main readme and algorithm readme update
2022-06-30 fw: add buzzer and startup tones
2022-06-30 fw: add beep when updating pos and when pressing buttons
2022-06-30 docs: removed old DS
2022-06-30 docs: updated DS
2022-06-30 fw fix: tracking algo works perfectly
2022-06-30 chore: fix typos
2022-06-30 chore: add control over available satellites
2022-07-02 notes: add Windows building process and Picotool
2022-07-03 add first draft latex report
2022-07-03 chore: updated readme
2022-07-04 docs: updated report
2022-07-04 docs: removed indent from report
2022-07-04 report: fix assembly and testing paragraphs and other changes
    other changes are increase linespread, add tocdepth limit, remove SALMO SOCIETY from title
2022-07-04 docs: scale image in order to suppress warnings
2022-07-04 docs: cover
2022-07-04 report: remove triangle from cover
2022-07-04 report: fix figures
2022-07-04 docs: gerbers
2022-07-04 docs: update report
2022-07-05 hw: add drill map pdf
2022-07-05 report revision
2022-07-11 fw: check satellites even with sun position computation
2022-07-11 docs: fix typos
2022-07-11 fw: startup tone more sobrio
